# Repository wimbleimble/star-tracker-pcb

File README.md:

# Twinkle Tracker PCB
Ths repostitory contains KiCAD files for the PCB for the Twinkle Tracker
astrophotography mount.

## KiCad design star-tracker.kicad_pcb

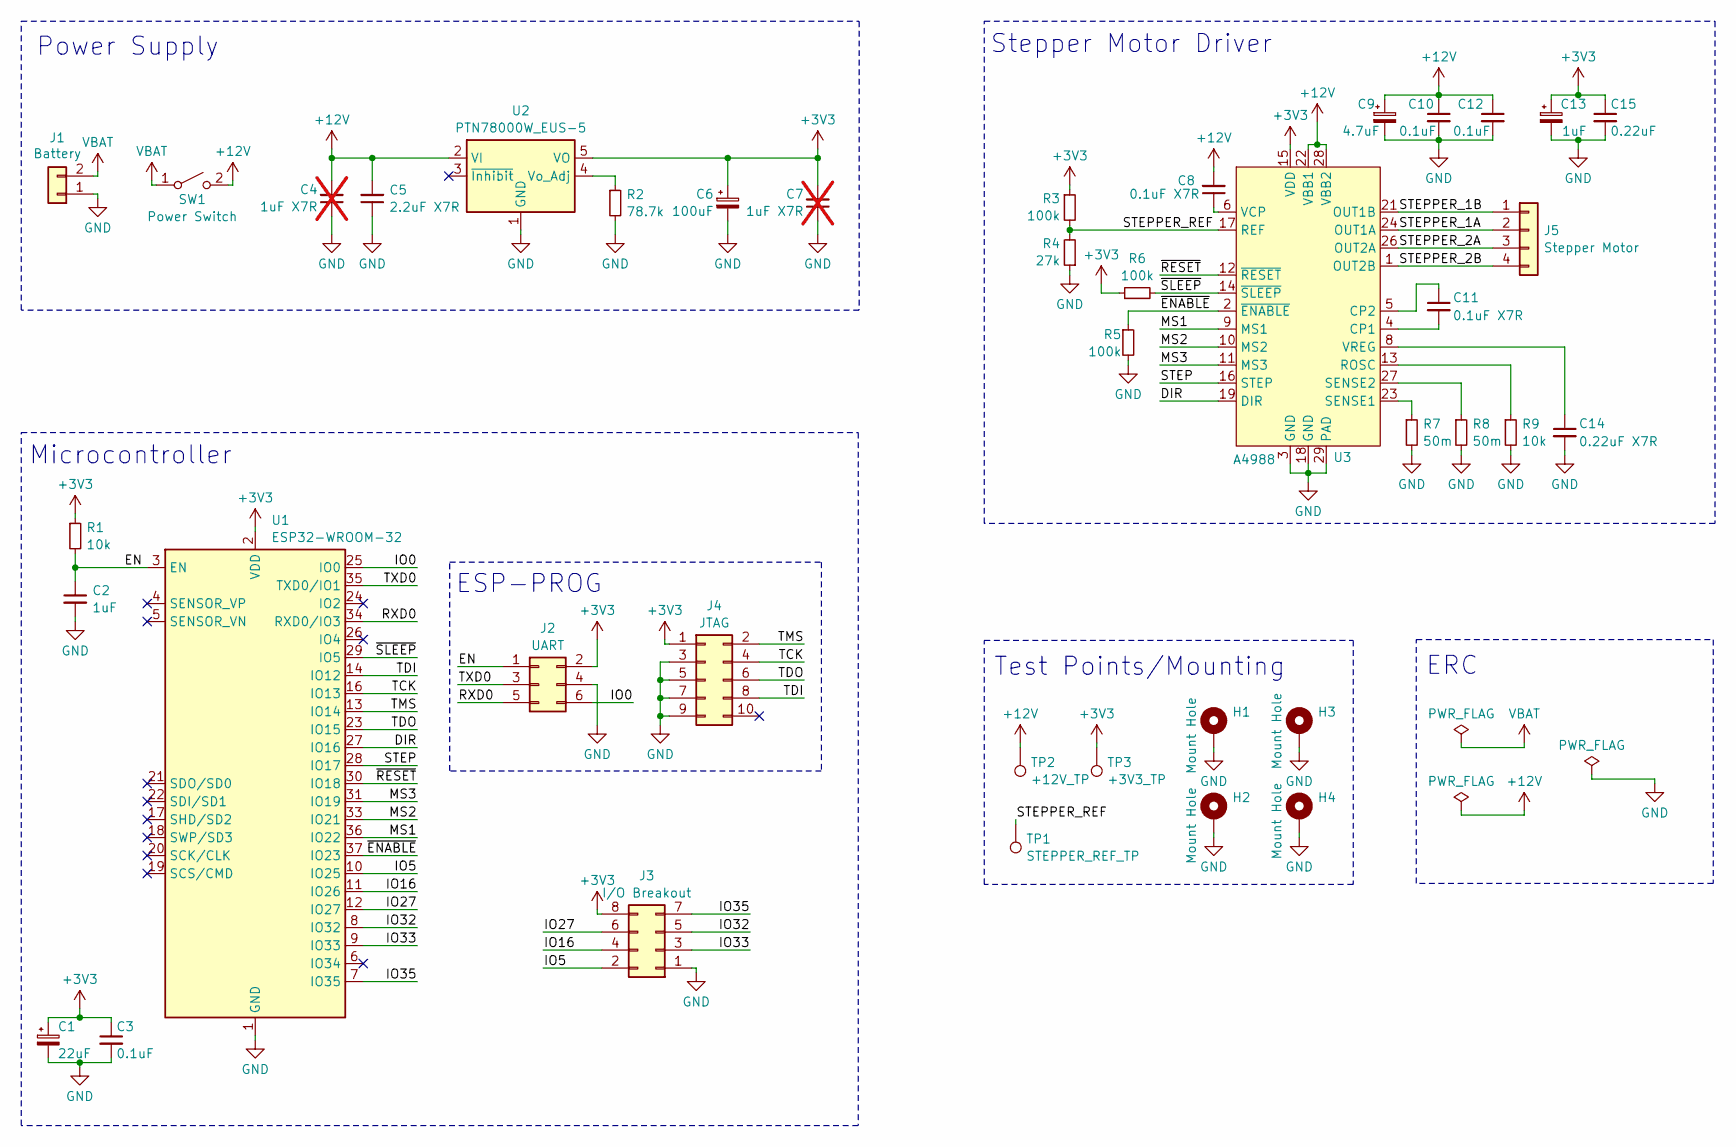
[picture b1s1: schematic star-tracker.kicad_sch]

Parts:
C1: 22uF; CP_Radial_D5.0mm_P2.00mm
C2: 1uF; C_0805_2012Metric_Pad1.18x1.45mm_HandSolder
C3, C10, C12: 0.1uF; C_0603_1608Metric_Pad1.08x0.95mm_HandSolder
C4, C7: 1uF X7R; C_0805_2012Metric_Pad1.18x1.45mm_HandSolder; not fitted
C5: 2.2uF X7R; C_0805_2012Metric_Pad1.18x1.45mm_HandSolder
C6: 100uF; CP_Radial_D6.3mm_P2.50mm
C8, C11: 0.1uF X7R; C_0603_1608Metric_Pad1.08x0.95mm_HandSolder
C9: 4.7uF; CP_Radial_D6.3mm_P2.50mm
C13: 1uF; CP_Radial_D5.0mm_P2.00mm
C14: 0.22uF X7R; C_0603_1608Metric_Pad1.08x0.95mm_HandSolder
C15: 0.22uF; C_0603_1608Metric_Pad1.08x0.95mm_HandSolder
H1, H2, H3, H4: Mount Hole; MountingHole_2.2mm_M2_Pad
J1: Battery; AMASS_XT60-M_1x02_P7.20mm_Vertical
J2: UART; PinHeader_2x03_P1.27mm_Vertical_SMD
J3: I/O Breakout; IDC-Header_2x04_P2.54mm_Vertical
J4: JTAG; PinHeader_2x05_P1.27mm_Vertical_SMD
J5: Stepper Motor; JST_XH_B4B-XH-A_1x04_P2.50mm_Vertical
R1, R9: 10k; R_0603_1608Metric_Pad0.98x0.95mm_HandSolder
R2: 78.7k; R_0603_1608Metric_Pad0.98x0.95mm_HandSolder; Tolerance 1%
R3, R5, R6: 100k; R_0603_1608Metric_Pad0.98x0.95mm_HandSolder
R4: 27k; R_0603_1608Metric_Pad0.98x0.95mm_HandSolder
R7, R8: 50m; R_0603_1608Metric_Pad0.98x0.95mm_HandSolder
SW1: Power Switch; PinHeader_1x02_P2.54mm_Vertical
TP1: STEPPER_REF_TP; TestPoint_THTPad_D2.0mm_Drill1.0mm
TP2: +12V_TP; TestPoint_THTPad_D2.0mm_Drill1.0mm
TP3: +3V3_TP; TestPoint_THTPad_D2.0mm_Drill1.0mm
U1: ESP32-WROOM-32
U2: PTN78000W_EUS-5; Texas_EUS_R-PDSS-T5_THT
U3: A4988; QFN-28-1EP_5x5mm_P0.5mm_EP3.1x3.1mm_ThermalVias

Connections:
+3V3: C1.1, C3.1, C6.1, C7.2, C13.1, C15.1, J2.2, J3.8, J4.1, R1.1, R3.1, R6.1, TP3.1, U1.2 (VDD), U2.5 (VO), U3.15 (VDD)
+12V: C4.2, C5.2, C8.2, C9.1, C10.1, C12.1, SW1.2 (B), TP2.1, U2.2 (VI), U3.22 (VBB1), U3.28 (VBB2)
/DIR: U1.27 (IO16), U3.19 (DIR)
/EN: C2.1, J2.1, R1.2, U1.3 (EN)
/IO0: J2.6, U1.25 (IO0)
/IO5: J3.2, U1.10 (IO25)
/IO16: J3.4, U1.11 (IO26)
/IO27: J3.6, U1.12 (IO27)
/IO32: J3.5, U1.8 (IO32)
/IO33: J3.3, U1.9 (IO33)
/IO35: J3.7, U1.7 (IO35)
/MS1: U1.36 (IO22), U3.9 (MS1)
/MS2: U1.33 (IO21), U3.10 (MS2)
/MS3: U1.31 (IO19), U3.11 (MS3)
/RXD0: J2.5, U1.34 (RXD0/IO3)
/STEP: U1.28 (IO17), U3.16 (STEP)
/STEPPER_1A: J5.2, U3.24 (OUT1A)
/STEPPER_1B: J5.1, U3.21 (OUT1B)
/STEPPER_2A: J5.3, U3.26 (OUT2A)
/STEPPER_2B: J5.4, U3.1 (OUT2B)
/STEPPER_REF: R3.2, R4.2, TP1.1, U3.17 (REF)
/TCK: J4.4, U1.16 (IO13)
/TDI: J4.8, U1.14 (IO12)
/TDO: J4.6, U1.23 (IO15)
/TMS: J4.2, U1.13 (IO14)
/TXD0: J2.3, U1.35 (TXD0/IO1)
/~ENABLE: R5.1, U1.37 (IO23), U3.2 (~ENABLE)
/~RESET: U1.30 (IO18), U3.12 (~RESET)
/~SLEEP: R6.2, U1.29 (IO5), U3.14 (~SLEEP)
GND: C1.2, C2.2, C3.2, C4.1, C5.1, C6.2, C7.1, C9.2, C10.2, C12.2, C13.2, C14.2, C15.2, H1.1, H2.1, H3.1, H4.1, J1.1, J2.4, J3.1, J4.3, J4.5, J4.7, J4.9, R2.2, R4.1, R5.2, R7.2, R8.2, R9.2, U1.1 (GND), U1.15 (GND), U1.38 (GND), U1.39 (GND), U2.1 (GND), U3.3 (GND), U3.18 (GND), U3.29 (PAD)
unnamed: R2.1, U2.4 (Vo_Adj)
unnamed: C11.2, U3.4 (CP1)
unnamed: C11.1, U3.5 (CP2)
unnamed: R9.1, U3.13 (ROSC)
unnamed: R7.1, U3.23 (SENSE1)
unnamed: R8.1, U3.27 (SENSE2)
unnamed: C8.1, U3.6 (VCP)
unnamed: C14.1, U3.8 (VREG)
VBAT: J1.2, SW1.1 (A)

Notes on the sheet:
Power Supply
Test Points/Mounting
Stepper Motor Driver
Microcontroller
ERC
ESP-PROG

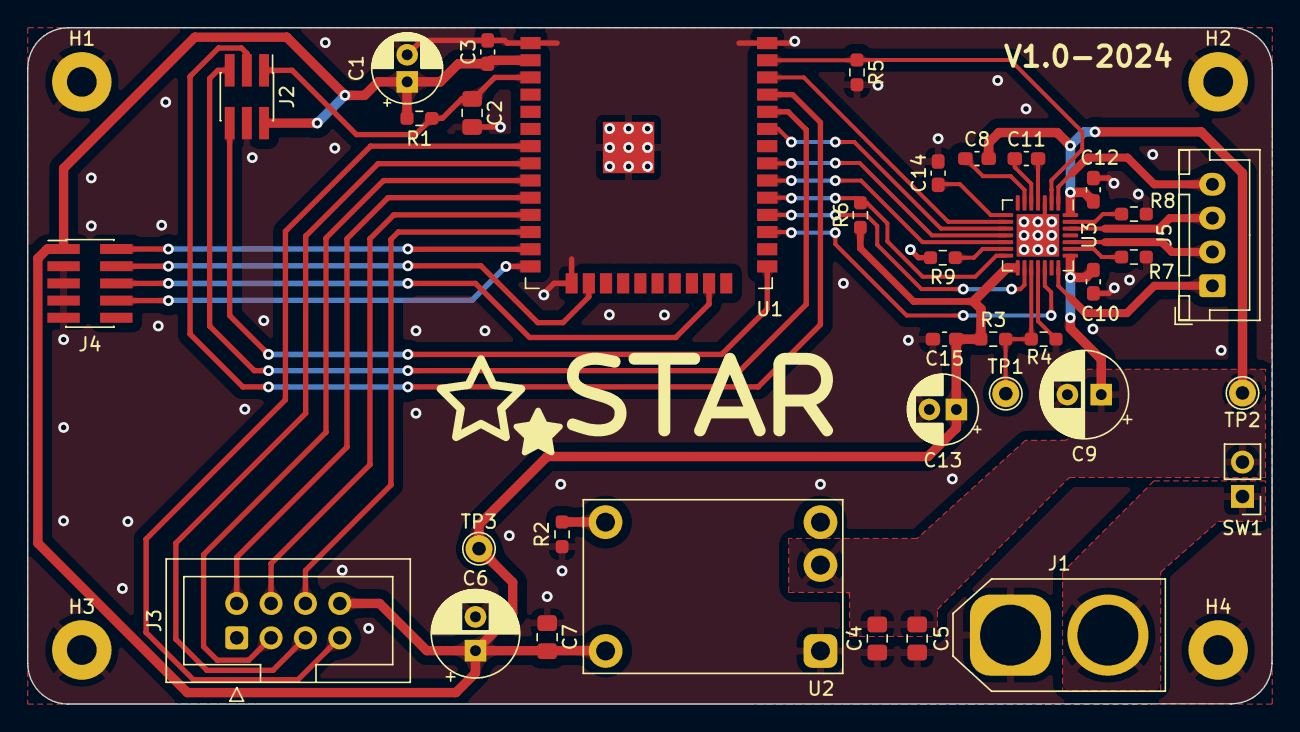
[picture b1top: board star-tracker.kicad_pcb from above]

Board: 2 copper layers, 92.0 x 50.0 mm, 40 parts (0 on the bottom side), 39 nets.

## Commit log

2024-03-03 Initial revision
2024-03-03 updated track widths, teardrops
2024-03-03 removed redundant files
2024-03-04 changed esp32 footprint
2024-03-05 some tweaks, footprint change
2024-04-19 added readme
